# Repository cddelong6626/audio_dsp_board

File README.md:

# audio_dsp_board

This board will take in audio input from either USB-C (2.0) or an audio jack and output processed audio through a separate audio jack. 

Stereo ADC/DAC provided by SGTL5000 audio codec. Data processing performed by STM32F405 microcontroller.

Image of board with 3D models from KiCad:

Image of board with 3D models from JLCPCB:

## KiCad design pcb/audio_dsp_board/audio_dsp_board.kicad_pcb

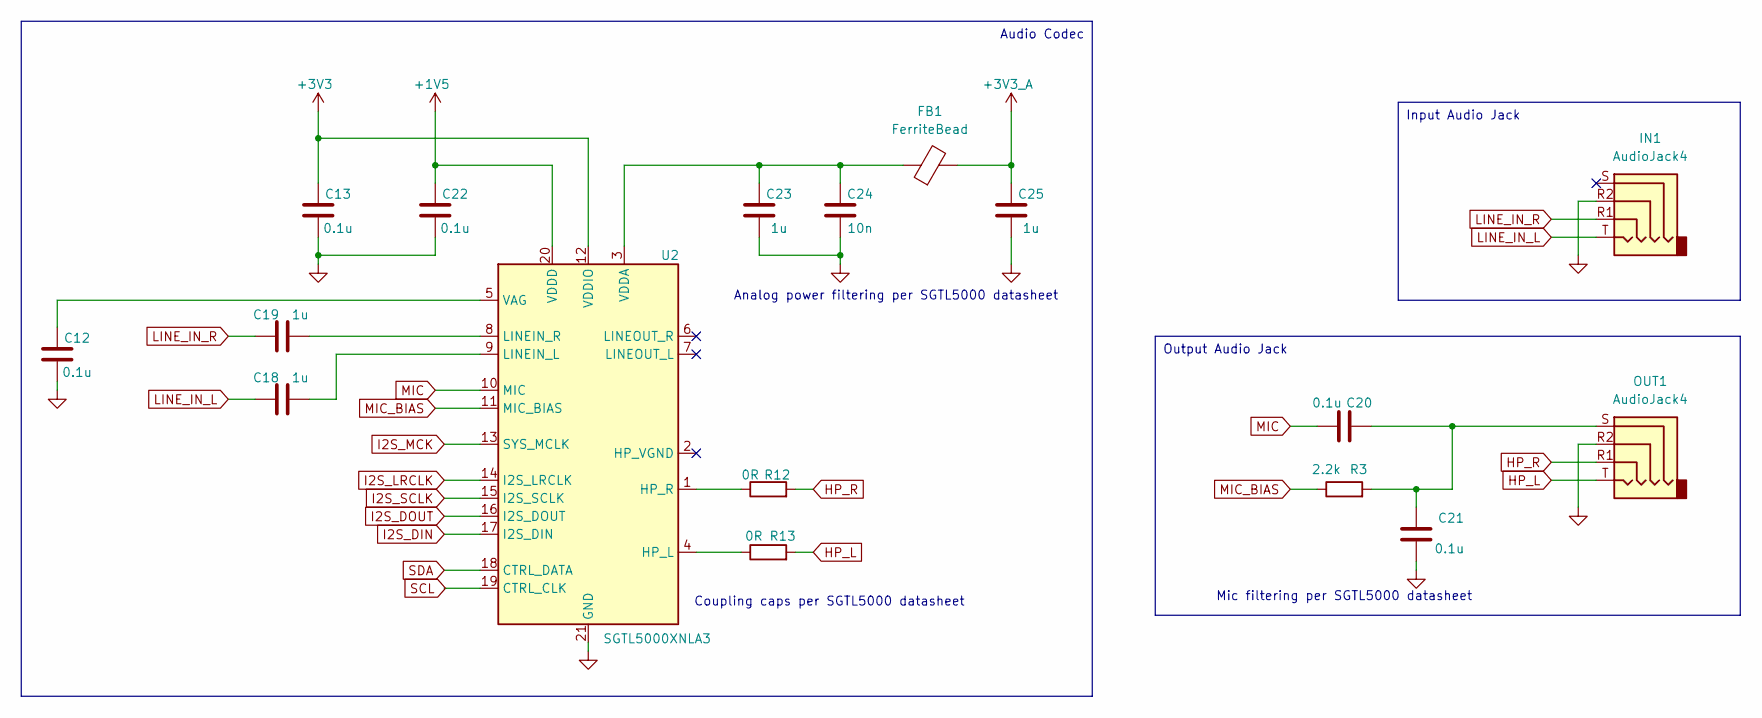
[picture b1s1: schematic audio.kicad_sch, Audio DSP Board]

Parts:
C12, C13, C20, C21, C22: 0.1u; C_0402_1005Metric
C18, C19, C23, C25: 1u; C_0402_1005Metric
C24: 10n; C_0402_1005Metric
FB1: FerriteBead; D_0603_1608Metric
IN1: AudioJack4; Jack_3.5mm_PJ320D_Horizontal
OUT1: AudioJack4; Jack_3.5mm_PJ320D_Horizontal
R3: 2.2k; R_0402_1005Metric
R12, R13: 0R; R_0805_2012Metric
U2: SGTL5000XNLA3; QFN-20-1EP_3x3mm_P0.4mm_EP1.65x1.65mm

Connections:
+1V5: C22.1, U2.20 (VDDD); also elsewhere on the board
+3V3: C13.1, U2.12 (VDDIO); also elsewhere on the board
+3V3_A: C25.1, FB1.2; also elsewhere on the board
GND: C12.2, C13.2, C21.2, C22.2, C23.2, C24.2, C25.2, IN1.R2, OUT1.R2, U2.21 (GND); also elsewhere on the board
HP_L: OUT1.T, R13.2
HP_R: OUT1.R1, R12.2
I2S_DIN: U2.17 (I2S_DIN); also elsewhere on the board
I2S_DOUT: U2.16 (I2S_DOUT); also elsewhere on the board
I2S_LRCLK: U2.14 (I2S_LRCLK); also elsewhere on the board
I2S_MCK: U2.13 (SYS_MCLK); also elsewhere on the board
I2S_SCLK: U2.15 (I2S_SCLK); also elsewhere on the board
LINE_IN_L: C18.1, IN1.T
LINE_IN_R: C19.1, IN1.R1
MIC: C20.2, U2.10 (MIC)
MIC_BIAS: R3.1, U2.11 (MIC_BIAS)
unnamed: C20.1, C21.1, OUT1.S, R3.2
unnamed: R13.1, U2.4 (HP_L)
unnamed: R12.1, U2.1 (HP_R)
unnamed: C18.2, U2.9 (LINEIN_L)
unnamed: C19.2, U2.8 (LINEIN_R)
unnamed: C12.1, U2.5 (VAG)
unnamed: C23.1, C24.1, FB1.1, U2.3 (VDDA)
SCL: U2.19 (CTRL_CLK); also elsewhere on the board
SDA: U2.18 (CTRL_DATA); also elsewhere on the board

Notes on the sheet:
Audio Codec
Output Audio Jack
Input Audio Jack
Analog power filtering per SGTL5000 datasheet
Mic filtering per SGTL5000 datasheet
Coupling caps per SGTL5000 datasheet

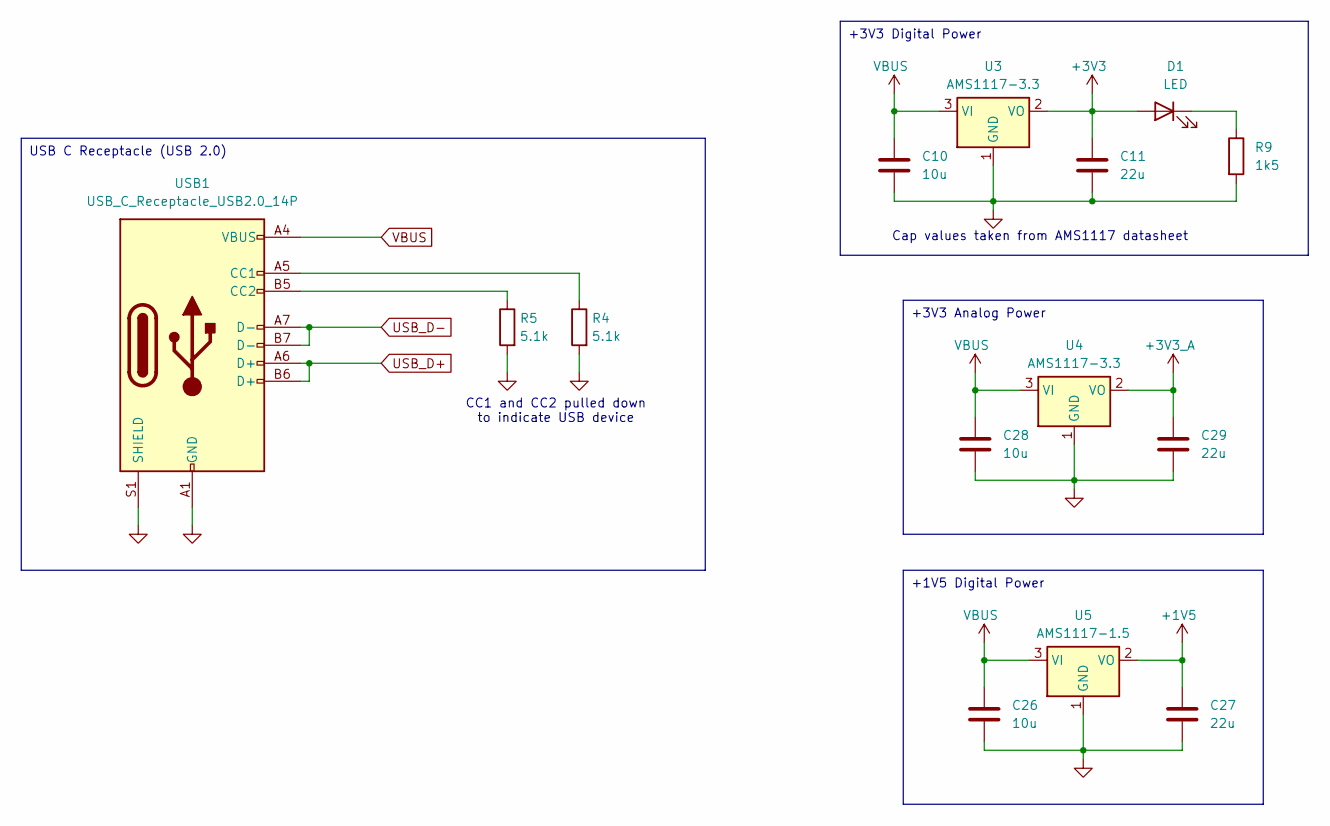
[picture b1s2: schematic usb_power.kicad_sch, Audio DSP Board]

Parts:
C10, C26, C28: 10u; C_0603_1608Metric
C11, C27, C29: 22u; C_0805_2012Metric
D1: LED; D_0603_1608Metric
R4, R5: 5.1k; R_0402_1005Metric
R9: 1k5; R_0402_1005Metric
U3, U4: AMS1117-3.3; SOT-223-3_TabPin2
U5: AMS1117-1.5; SOT-223-3_TabPin2
USB1: USB_C_Receptacle_USB2.0_14P; USB_C_Receptacle_XKB_U262-16XN-4BVC11

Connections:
+1V5: C27.1, U5.2 (VO); also elsewhere on the board
+3V3: C11.1, D1.2 (A), U3.2 (VO); also elsewhere on the board
+3V3_A: C29.1, U4.2 (VO); also elsewhere on the board
GND: C10.2, C11.2, C26.2, C27.2, C28.2, C29.2, R4.2, R5.2, R9.2, U3.1 (GND), U4.1 (GND), U5.1 (GND), USB1.A1 (GND), USB1.A12 (GND), USB1.B1 (GND), USB1.B12 (GND), USB1.S1 (SHIELD); also elsewhere on the board
unnamed: D1.1 (K), R9.1
unnamed: R4.1, USB1.A5 (CC1)
unnamed: R5.1, USB1.B5 (CC2)
USB_D+: USB1.A6 (D+), USB1.B6 (D+); also elsewhere on the board
USB_D-: USB1.A7 (D-), USB1.B7 (D-); also elsewhere on the board
VBUS: C10.1, C26.1, C28.1, U3.3 (VI), U4.3 (VI), U5.3 (VI), USB1.A4 (VBUS), USB1.A9 (VBUS), USB1.B4 (VBUS), USB1.B9 (VBUS)

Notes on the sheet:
+1V5 Digital Power
USB C Receptacle (USB 2.0)
+3V3 Analog Power
+3V3 Digital Power
Cap values taken from AMS1117 datasheet
CC1 and CC2 pulled down to indicate USB device

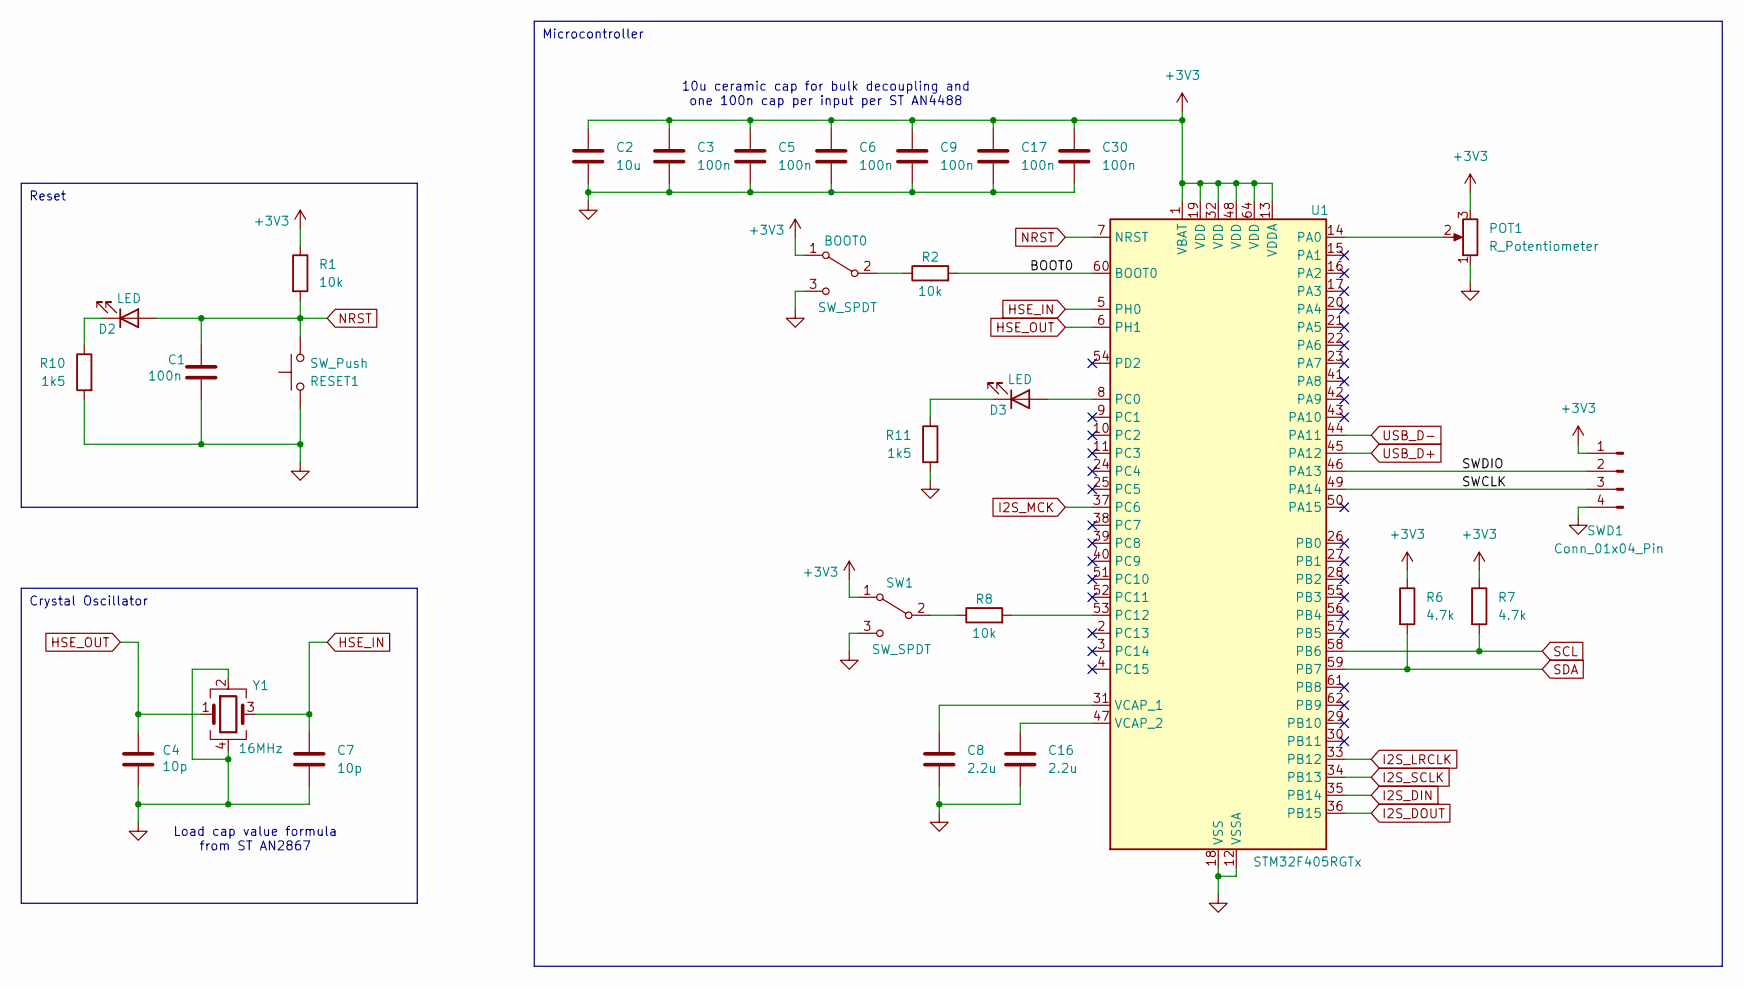
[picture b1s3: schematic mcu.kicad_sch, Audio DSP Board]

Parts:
BOOT0: SW_SPDT; SW_SPDT_PCM12
C1, C3, C5, C6, C9, C17, C30: 100n; C_0402_1005Metric
C2: 10u; C_0603_1608Metric
C4, C7: 10p; C_0402_1005Metric
C8, C16: 2.2u; C_0402_1005Metric
D2, D3: LED; D_0603_1608Metric
POT1: R_Potentiometer; TRIM_3362P-1-103LF
R1, R2, R8: 10k; R_0402_1005Metric
R6, R7: 4.7k; R_0402_1005Metric
R10, R11: 1k5; R_0402_1005Metric
RESET1: SW_Push; EL23520JLFS
SW1: SW_SPDT; SW_SPDT_PCM12
SWD1: Conn_01x04_Pin; PinHeader_1x04_P2.54mm_Vertical
U1: STM32F405RGTx; LQFP-64_10x10mm_P0.5mm
Y1: 16MHz; Crystal_SMD_3225-4Pin_3.2x2.5mm

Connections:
+3V3: BOOT0.1 (A), C2.1, C3.1, C5.1, C6.1, C9.1, C17.1, C30.1, POT1.3, R1.1, R6.1, R7.1, SW1.1 (A), SWD1.1, U1.1 (VBAT), U1.13 (VDDA), U1.19 (VDD), U1.32 (VDD), U1.48 (VDD), U1.64 (VDD); also elsewhere on the board
/MCU/BOOT0: R2.2, U1.60 (BOOT0)
/MCU/SWCLK: SWD1.3, U1.49 (PA14)
/MCU/SWDIO: SWD1.2, U1.46 (PA13)
GND: BOOT0.3 (C), C1.2, C2.2, C3.2, C4.2, C5.2, C6.2, C7.2, C8.2, C9.2, C16.2, C17.2, C30.2, POT1.1, R10.2, R11.2, RESET1.2, SW1.3 (C), SWD1.4, U1.12 (VSSA), U1.18 (VSS), U1.63 (VSS), Y1.2, Y1.4; also elsewhere on the board
HSE_IN: C7.1, U1.5 (PH0), Y1.3
HSE_OUT: C4.1, U1.6 (PH1), Y1.1
I2S_DIN: U1.35 (PB14); also elsewhere on the board
I2S_DOUT: U1.36 (PB15); also elsewhere on the board
I2S_LRCLK: U1.33 (PB12); also elsewhere on the board
I2S_MCK: U1.37 (PC6); also elsewhere on the board
I2S_SCLK: U1.34 (PB13); also elsewhere on the board
NRST: C1.1, D2.2 (A), R1.2, RESET1.1, U1.7 (NRST)
unnamed: BOOT0.2 (B), R2.1
unnamed: D2.1 (K), R10.1
unnamed: D3.2 (A), U1.8 (PC0)
unnamed: D3.1 (K), R11.1
unnamed: R8.1, SW1.2 (B)
unnamed: POT1.2, U1.14 (PA0)
unnamed: R8.2, U1.53 (PC12)
unnamed: C8.1, U1.31 (VCAP_1)
unnamed: C16.1, U1.47 (VCAP_2)
SCL: R7.2, U1.58 (PB6); also elsewhere on the board
SDA: R6.2, U1.59 (PB7); also elsewhere on the board
USB_D+: U1.45 (PA12); also elsewhere on the board
USB_D-: U1.44 (PA11); also elsewhere on the board

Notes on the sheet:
Crystal Oscillator
Microcontroller
Reset
Load cap value formula from ST AN2867
10u ceramic cap for bulk decoupling and one 100n cap per input per ST AN4488

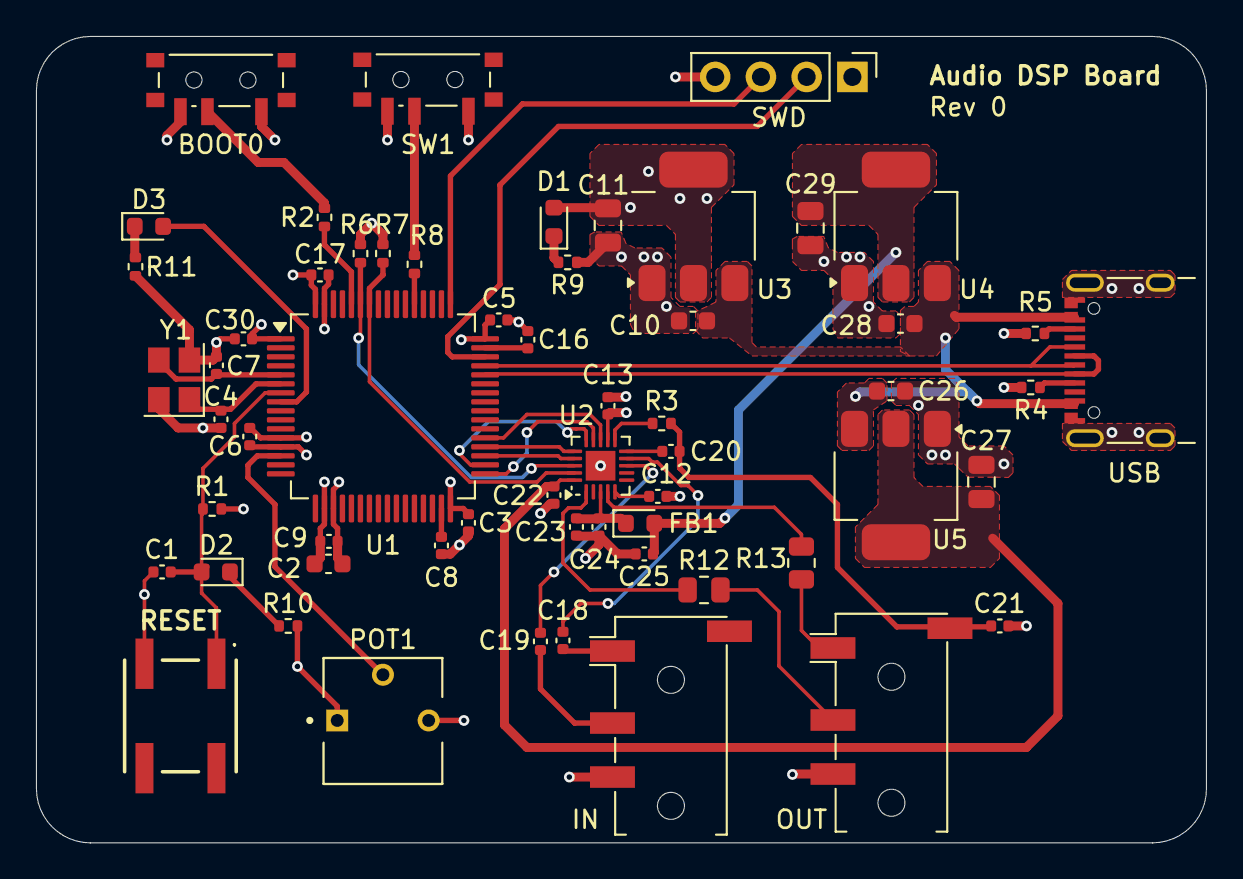
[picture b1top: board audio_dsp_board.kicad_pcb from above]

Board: 4 copper layers, 65.0 x 44.8 mm, 59 parts (0 on the bottom side), 45 nets.

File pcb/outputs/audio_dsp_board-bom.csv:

"Reference","Value","Datasheet","Footprint","Qty","DNP", "LCSC Part Number"
"C1,C3,C5,C6,C9,C17,C30","100n","~","Capacitor_SMD:C_0402_1005Metric","7","C1581"
"C2,C10,C26,C28","10u","~","Capacitor_SMD:C_0603_1608Metric","4","C15499"
"C4,C7","10p","~","Capacitor_SMD:C_0402_1005Metric","2","C32949"
"C8,C16","2.2u","~","Capacitor_SMD:C_0402_1005Metric","2","C12530"
"C11,C27,C29","22u","~","Capacitor_SMD:C_0805_2012Metric","3","C5674"
"C12,C13,C20,C21,C22","0.1u","~","Capacitor_SMD:C_0402_1005Metric","5","C141382"
"C18,C19,C23,C25","1u","~","Capacitor_SMD:C_0402_1005Metric","4","C14445"
"C24","10n","~","Capacitor_SMD:C_0402_1005Metric","1","C1524"
"D1,D2,D3","LED","~","Diode_SMD:D_0603_1608Metric","3","C20785"
"FB1","FerriteBead","~","Diode_SMD:D_0603_1608Metric","1","C1002"
"IN1,OUT1","AudioJack4","~","Connector_Audio:Jack_3.5mm_PJ320D_Horizontal","2","C431535"
"SWD1","Conn_01x04_Pin","~","Connector_PinHeader_2.54mm:PinHeader_1x04_P2.54mm_Vertical","1","C2905435"
"USB1","USB_C_Receptacle_USB2.0_14P","https://www.usb.org/sites/default/files/documents/usb_type-c.zip","Connector_USB:USB_C_Receptacle_XKB_U262-16XN-4BVC11","1","C319148"
"R1,R2,R8","10k","~","Resistor_SMD:R_0402_1005Metric","3","C60490"
"R3","2.2k","~","Resistor_SMD:R_0402_1005Metric","1","C102890"
"R4,R5","5.1k","~","Resistor_SMD:R_0402_1005Metric","2","C103079"
"R6,R7","4.7k","~","Resistor_SMD:R_0402_1005Metric","2","C25900"
"R9,R10,R11","1k5","~","Resistor_SMD:R_0402_1005Metric","3","C25867"
"R12,R13","0R","~","Resistor_SMD:R_0805_2012Metric","2","C1297"
"POT1","R_Potentiometer","~","AAA:TRIM_3362P-1-103LF","1","C58159"
"RESET1","SW_Push","~","AAA:EL23520JLFS","1","C36364017"
"BOOT0,SW1","SW_SPDT","~","Button_Switch_SMD:SW_SPDT_PCM12","2","C221841"
"U1","STM32F405RGTx","https://www.st.com/resource/en/datasheet/stm32f405rg.pdf","Package_QFP:LQFP-64_10x10mm_P0.5mm","1","C15742"
"U2","SGTL5000XNLA3","https://www.nxp.com/docs/en/data-sheet/SGTL5000.pdf","Package_DFN_QFN:QFN-20-1EP_3x3mm_P0.4mm_EP1.65x1.65mm","1","C2802658"
"U3,U4","AMS1117-3.3","http://www.advanced-monolithic.com/pdf/ds1117.pdf","Package_TO_SOT_SMD:SOT-223-3_TabPin2","2","C6186"
"U5","AMS1117-1.5","http://www.advanced-monolithic.com/pdf/ds1117.pdf","Package_TO_SOT_SMD:SOT-223-3_TabPin2","1","C16172"
"Y1","16MHz","https://www.lcsc.com/datasheet/lcsc_datasheet_2409301532_YXC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","Crystal:Crystal_SMD_3225-4Pin_3.2x2.5mm","1","C12668"

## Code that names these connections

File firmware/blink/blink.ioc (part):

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Mcu.Name=STM32F405RGTx
Mcu.Package=LQFP64
Mcu.UserName=STM32F405RGTx
PA0-WKUP.Signal=ADCx_IN0
PA10.Mode=OTG/Dual_Role_Device
PA10.Signal=USB_OTG_FS_ID
PA11.Mode=OTG/Dual_Role_Device
PA11.Signal=USB_OTG_FS_DM
PA12.Mode=OTG/Dual_Role_Device
PA12.Signal=USB_OTG_FS_DP
PA13.Mode=Serial_Wire
PA13.Signal=SYS_JTMS-SWDIO
PA14.Mode=Serial_Wire
PA14.Signal=SYS_JTCK-SWCLK
PB12.Mode=Full_Duplex_Master
PB12.Signal=I2S2_WS
PB13.Mode=Full_Duplex_Master
PB13.Signal=I2S2_CK
PB14.Mode=Full_Duplex_Master
PB14.Signal=I2S2_ext_SD
PB15.Mode=Full_Duplex_Master
PB15.Signal=I2S2_SD
PB6.Mode=I2C
PB6.Signal=I2C1_SCL
PB7.Mode=I2C
PB7.Signal=I2C1_SDA
PC0.Signal=GPIO_Output
PC12.Signal=GPIO_Input
PC6.Mode=Master_Clock_Activated
PC6.Signal=I2S2_MCK
PH0-OSC_IN.Mode=HSE-External-Oscillator
PH0-OSC_IN.Signal=RCC_OSC_IN
PH1-OSC_OUT.Mode=HSE-External-Oscillator
PH1-OSC_OUT.Signal=RCC_OSC_OUT
RCC.HSE_VALUE=16000000
RCC.SYSCLKFreq_VALUE=168000000
RCC.SYSCLKSource=RCC_SYSCLKSOURCE_PLLCLK
board=custom

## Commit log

2024-10-07 pcb files initial commit
2024-10-07 firmware initial commit
2024-10-16 Rough draft of schematic capture done
2024-10-29 Schematic capture, placement, routing complete
    Sending board to JLCPCB for manufacturing and assembly.
2025-02-28 Add blink software
    Add an stm32cubeide project that toggles LED3 every 0.5 seconds.
2025-03-04 Finish PCB and add basic firmware
    Finish creating PCB, add 2 STM32 projects:
    blink: blinks LED D3
    pot_led_pwm: Controls LED D3 dimming using POT1 and PWM
2025-03-14 Create .gitignore
    Add templates to .gitignore unneeded stm32cubeide and KiCad files.
